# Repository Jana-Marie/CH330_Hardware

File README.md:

# CH330_Hardware USB-UART Converter

I created this board because I wanted to play with the CH330N because it was supposed to be a crystal-less, <$0.35 USB UART converter in a SOIC-8 package. Since these chips were available from LCSC, I created a quick design and ordered both together.

As the IC is very small (other USB UART converters are packed in at least a QFN or SOIC-16), I didn't want the board to get much bigger. Accordingly, I developed this 10*10mm USB UART converter board with the CH330N and micro-USB. The assembly is quite fiddly, I suggest that you reflow the USB port and then solder the CH330N (and the LEDs) by hand. If you want to order these boards, I recommend you panelize them.

The CH330N enumerates as CH340 or CH341 and its transfer speed goes up to ~2Mb/s.

#### [More Info (Twitter Link)](https://twitter.com/_Jana_Marie/status/1057014341155872769)
#### [This project on Kitspace.org](https://kitspace.org/boards/github.com/jana-marie/ch330_hardware/)

### Images

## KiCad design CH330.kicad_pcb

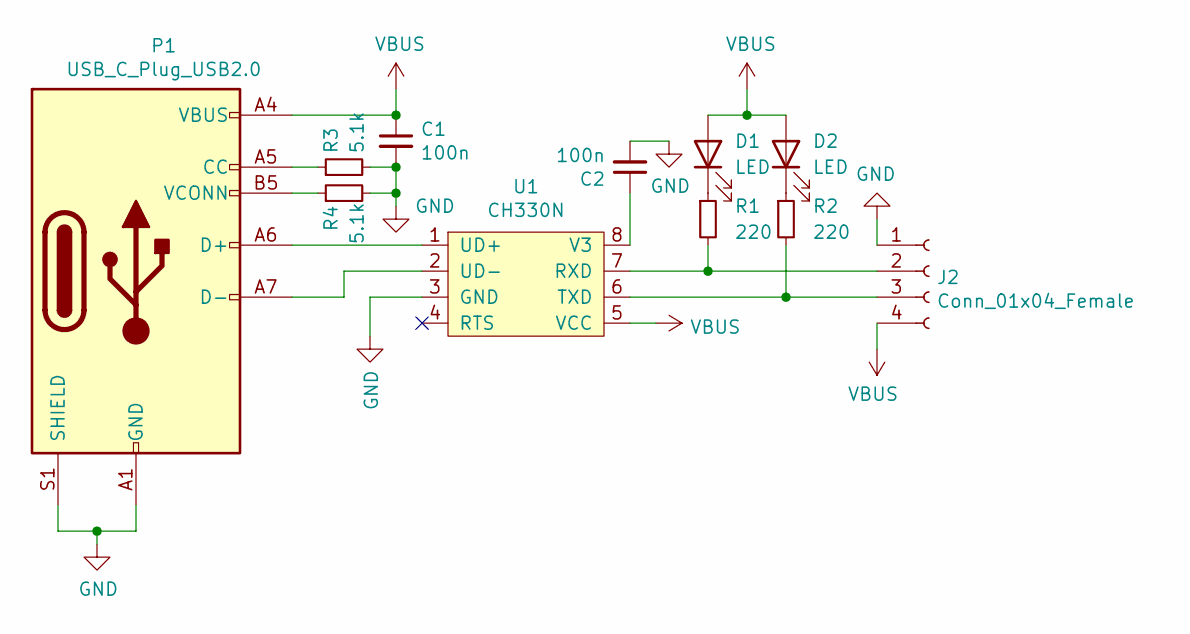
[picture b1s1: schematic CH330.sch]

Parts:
C1, C2: 100n; C_0603_1608Metric; Mfr. Part CC0603KRX7R9BB104
D1, D2: LED; LED_0603_1608Metric; Mfr. Part 19-217/R6C-AL1M2VY/3T
J2: Conn_01x04_Female; PinHeader_1x04_P2.54mm_Vertical
P1: USB_C_Plug_USB2.0; USB_C_Receptacle_XKB_U262-16XN-4BVC11; Mfr. Part U262-161N-4BVC11
R1, R2: 220; R_0603_1608Metric; Mfr. Part 0603WAF2200T5E
R3, R4: 5.1k; R_0603_1608Metric; Mfr. Part 0603WAJ0512T5E
U1: CH330N; SOIC-8_3.9x4.9mm_P1.27mm; Mfr. Part CH330N

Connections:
GND: C1.2, C2.2, J2.1, P1.A1 (GND), P1.A12 (GND), P1.B1 (GND), P1.B12 (GND), P1.S1 (SHIELD), R3.2, R4.2, U1.3 (GND)
unnamed: C2.1, U1.8 (V3)
unnamed: D1.1 (K), R1.1
unnamed: D2.1 (K), R2.1
unnamed: J2.2, R1.2, U1.7 (RXD)
unnamed: J2.3, R2.2, U1.6 (TXD)
unnamed: P1.A5 (CC), R3.1
unnamed: P1.A6 (D+), U1.1 (UD+)
unnamed: P1.A7 (D-), U1.2 (UD-)
unnamed: P1.B5 (VCONN), R4.1
VBUS: C1.1, D1.2 (A), D2.2 (A), J2.4, P1.A4 (VBUS), P1.A9 (VBUS), P1.B4 (VBUS), P1.B9 (VBUS), U1.5 (VCC)

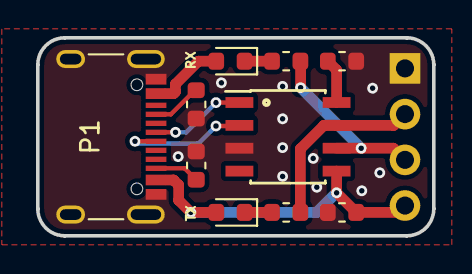
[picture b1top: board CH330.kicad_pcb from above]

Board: 2 copper layers, 22.0 x 11.0 mm, 11 parts (0 on the bottom side), 11 nets.

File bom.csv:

References,Qty,Description,Manufacturer,MPN,Digikey,Mouser,RS,Newark,Farnell
"C1,C2",2,0.1µF 0603 50V,AVX,06035G104ZAT2A,311-1344-1-ND,603CC603KRX7R9BB104,1358345,96M1293,1288255
"D1,D2",2,LED 0603,Everlight,19-217/BHC-ZL1M2RY/3T,160-1183-1-ND,859LTSTC190GKT,6910451,68Y1165,1652108
J1,1,Micro USB,,,A97800CT-ND,57119815681,6694645,73M8666,2751670
J2,1,PinHeader 4 pin,,,WM2746-ND,53822292041,6701333,26H2000,1360132
"R1,R2",2,220R 0603 0.25W,,,P220BYDKR-ND,,8626833,85Y6302,2335874
U1,1,CH330 SOIC-8,,https://lcsc.com/product-detail/USB_CH330N_C108996.html,,,,,

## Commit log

2018-10-29 added KiCAD files
2018-10-29 added Images
2018-10-29 updated images
2018-10-29 added gerber
2018-10-29 updated PCB
2018-12-16 Create LICENSE
2019-02-14 bom.csv
2019-02-14 moved bom
2019-02-14 added kitspace.yaml
2019-02-14 updated bom
2019-02-14 updated kitspace.yaml
2019-02-14 added 1-click bom
2021-01-08 add: gitignore
2021-01-08 add: update schematics to USB C
2021-01-08 add: BOM
2021-01-08 add: pcb layout
2021-01-09 doc: update readme
2021-01-09 refactor: remove files added to gitignore
2021-01-09 add: USB-C port 3D model
2021-01-09 add: round corners 3D model adjustments
2021-01-09 add: 3D models of the board
2021-01-09 fix: minor fixes to pcb
2021-01-09 add: 3D Render image to readme
2021-01-09 fix: a few types in README
2021-01-09 refactor: remove old BOM and kitspace config
2021-01-09 add: BOM to README
2022-11-30 Update readme images
